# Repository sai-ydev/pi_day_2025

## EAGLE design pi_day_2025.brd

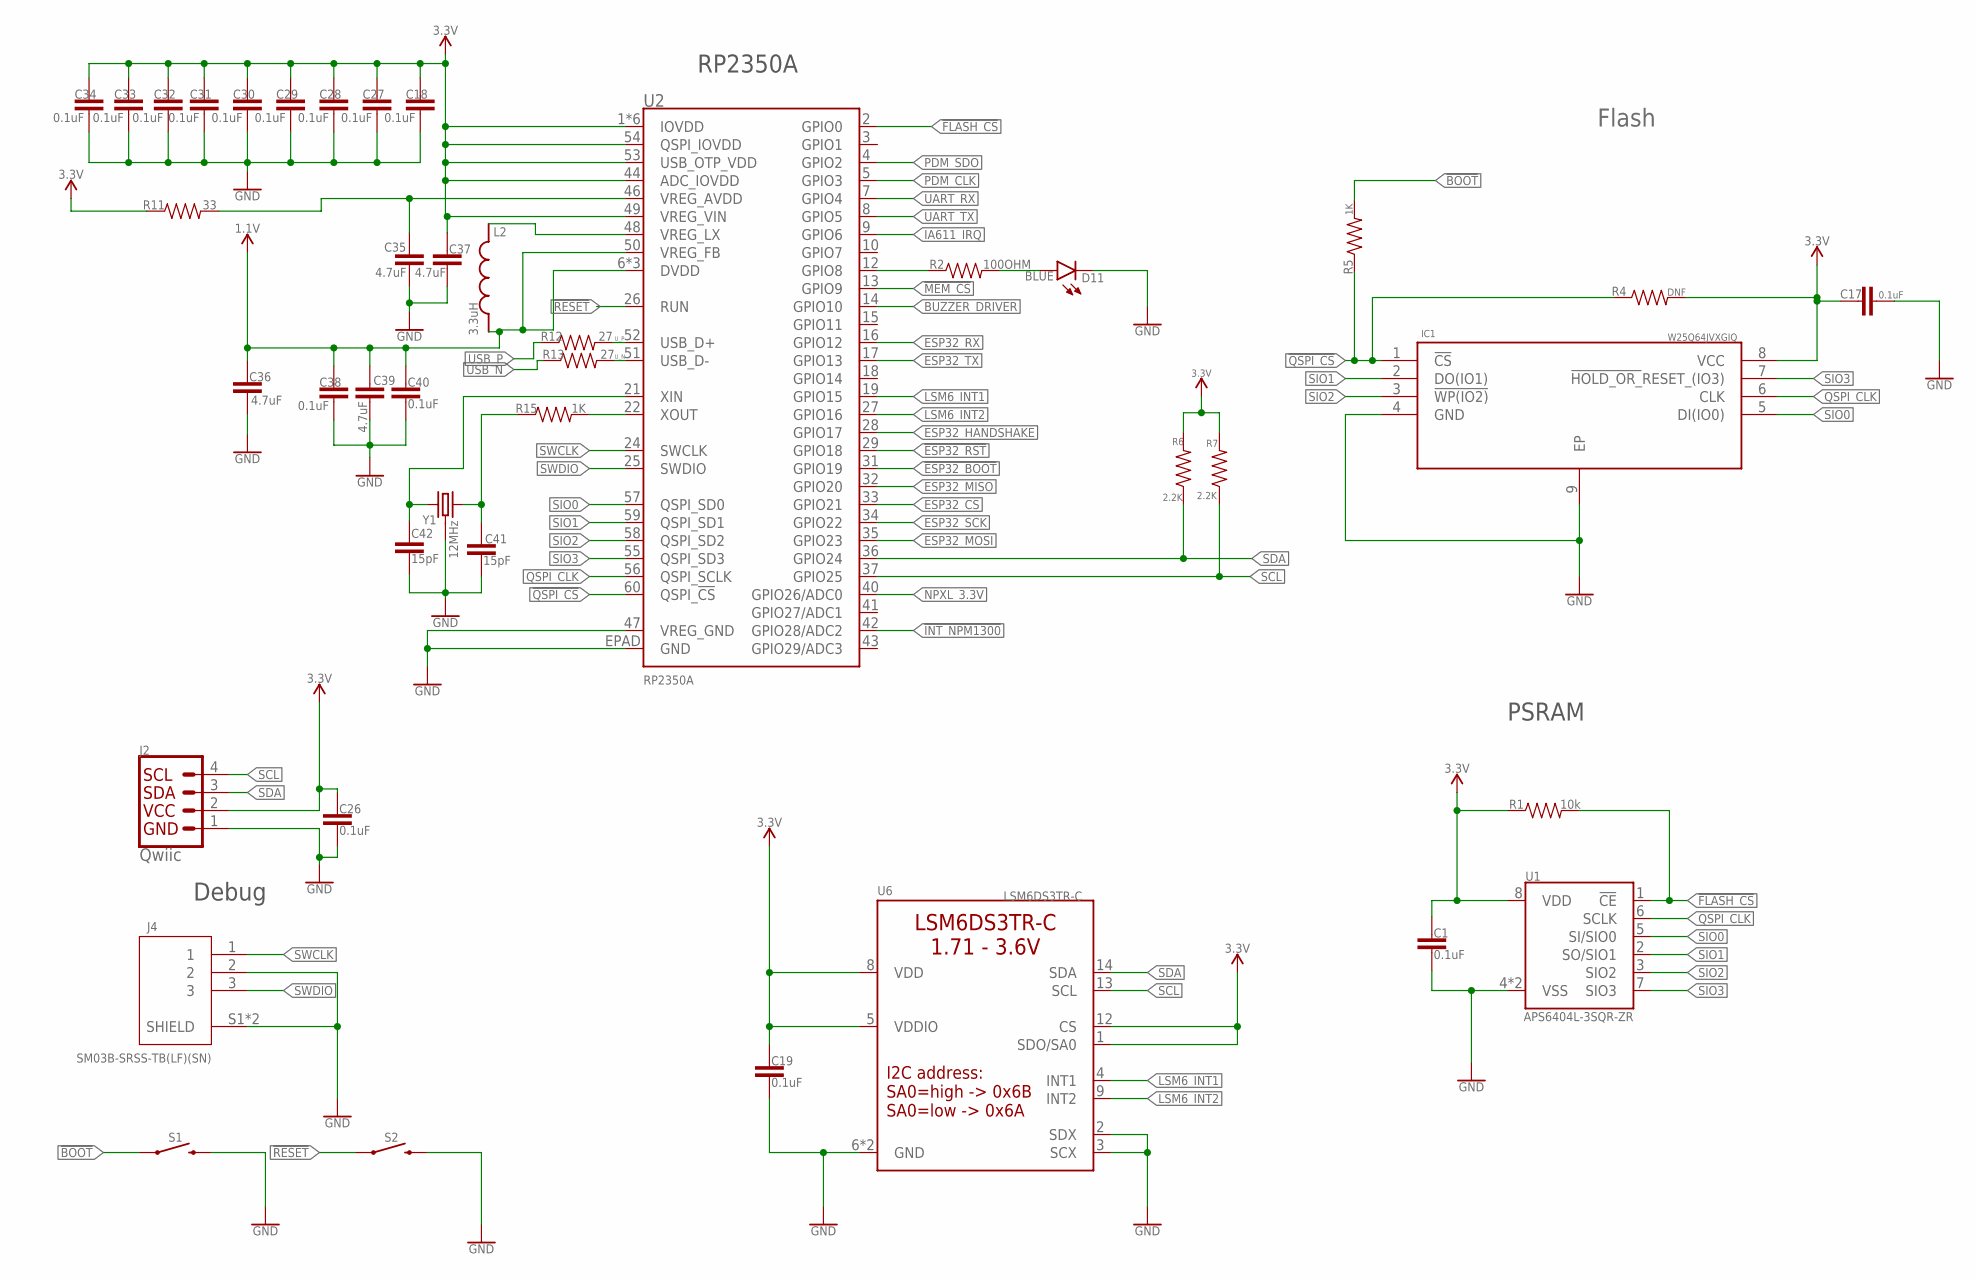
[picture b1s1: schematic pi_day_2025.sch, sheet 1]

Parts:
C1, C17, C18, C19, C26, C27, C28, C29, C30, C31, C32, C33, C34, C38, C40: 0.1uF; 0402
C35, C36, C37, C39: 4.7uF; 0402
C41, C42: 15pF; 0402
D11: BLUE; LED-0603
IC1: W25Q64JVXGIQ; SON80P400X400X50-9N
J2: Qwiic; 1X04_1MM_RA
J4: SM03B-SRSS-TB(LF)(SN); JST_SM03B-SRSS-TB(LF)(SN)
L2: 3.3uH; IND_LQH2MCN120K02L
R1: 10k; 0402
R2: 100OHM; 0402
R4: DNF; 0402
R5, R15: 1K; 0402
R6, R7: 2.2K; 0402
R11: 33; 0402
R12, R13: 27; 0402
S1, S2: MOMENTARY-SWITCH-SPST-SMD-4.6X2.8MM; TACTILE_SWITCH_SMD_4.6X2.8MM
U1: APS6404L-3SQR-ZR
U2: RP2350A
U6: LSM6DS3TR-C; LGA-14-2.5X3MM
Y1: 12MHz; CRYSTAL-SMD-3.2X2.5MM

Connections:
1.1V: C36.1, C38.1, C39.1, C40.1, L2.1, U2.6 (DVDD), U2.23 (DVDD), U2.39 (DVDD), U2.50 (VREG_FB)
3.3V: C1.1, C17.1, C18.1, C19.1, C26.1, C27.1, C28.1, C29.1, C30.1, C31.1, C32.1, C33.1, C34.1, C37.1, IC1.8 (VCC), J2.2, R1.1, R4.2, R6.2, R7.2, R11.1, U1.8 (VDD), U2.1 (IOVDD), U2.11 (IOVDD), U2.20 (IOVDD), U2.30 (IOVDD), U2.38 (IOVDD), U2.44 (ADC_IOVDD), U2.45 (IOVDD), U2.49 (VREG_VIN), U2.53 (USB_OTP_VDD), U2.54 (QSPI_IOVDD), U6.1 (SDO/SA0), U6.5 (VDDIO), U6.8 (VDD), U6.12 (CS); also elsewhere on the board
!BOOT: R5.2, S1.1, S1.2 (1)
!ESP32_BOOT: U2.31 (GPIO19); also elsewhere on the board
!ESP32_RST: U2.29 (GPIO18); also elsewhere on the board
!FLASH_CS: R1.2, U1.1 (!CE!), U2.2 (GPIO0)
!INT_NPM1300: U2.42 (GPIO28/ADC2); also elsewhere on the board
!MEM_CS: U2.13 (GPIO9); also elsewhere on the board
!QSPI_CS: IC1.1 (!CS), R4.1, R5.1, U2.60 (QSPI_!CS!)
!RESET: S2.1, S2.2 (1), U2.26 (RUN)
BUZZER_DRIVER: U2.14 (GPIO10); also elsewhere on the board
ESP32_CS: U2.33 (GPIO21); also elsewhere on the board
ESP32_HANDSHAKE: U2.28 (GPIO17); also elsewhere on the board
ESP32_MISO: U2.32 (GPIO20); also elsewhere on the board
ESP32_MOSI: U2.35 (GPIO23); also elsewhere on the board
ESP32_RX: U2.16 (GPIO12); also elsewhere on the board
ESP32_SCK: U2.34 (GPIO22); also elsewhere on the board
ESP32_TX: U2.17 (GPIO13); also elsewhere on the board
GND: C1.2, C17.2, C18.2, C19.2, C26.2, C27.2, C28.2, C29.2, C30.2, C31.2, C32.2, C33.2, C34.2, C35.2, C36.2, C37.2, C38.2, C39.2, C40.2, C41.2, C42.2, D11.C, IC1.4 (GND), IC1.9 (EP), J2.1, J4.2, J4.S1 (SHIELD), J4.S2 (SHIELD), S1.3 (2), S1.4 (2), S2.3 (2), S2.4 (2), U1.4 (VSS), U1.9 (VSS), U2.47 (VREG_GND), U2.EPAD (GND), U6.2 (SDX), U6.3 (SCX), U6.6 (GND), U6.7 (GND), Y1.2 (GND), Y1.4 (GND); also elsewhere on the board
IA611_IRQ: U2.9 (GPIO6); also elsewhere on the board
LSM6_INT1: U2.19 (GPIO15), U6.4 (INT1)
LSM6_INT2: U2.27 (GPIO16), U6.9 (INT2)
unnamed: R2.1, U2.12 (GPIO8)
unnamed: C35.1, R11.2, U2.46 (VREG_AVDD)
unnamed: D11.A, R2.2
unnamed: L2.2, U2.48 (VREG_LX)
unnamed: C41.1, R15.1, Y1.3 (2)
unnamed: C42.1, U2.21 (XIN), Y1.1
unnamed: R15.2, U2.22 (XOUT)
NPXL_3.3V: U2.40 (GPIO26/ADC0); also elsewhere on the board
PDM_CLK: U2.5 (GPIO3); also elsewhere on the board
PDM_SDO: U2.4 (GPIO2); also elsewhere on the board
QSPI_CLK: IC1.6 (CLK), U1.6 (SCLK), U2.56 (QSPI_SCLK)
SCL: J2.4, R7.1, U2.37 (GPIO25), U6.13 (SCL); also elsewhere on the board
SDA: J2.3, R6.1, U2.36 (GPIO24), U6.14 (SDA); also elsewhere on the board
SIO0: IC1.5 (DI(IO0)), U1.5 (SI/SIO0), U2.57 (QSPI_SD0)
SIO1: IC1.2 (DO(IO1)), U1.2 (SO/SIO1), U2.59 (QSPI_SD1)
SIO2: IC1.3 (!WP(IO2)), U1.3 (SIO2), U2.58 (QSPI_SD2)
SIO3: IC1.7 (!HOLD_OR_!RESET_(IO3)), U1.7 (SIO3), U2.55 (QSPI_SD3)
SWCLK: J4.1, U2.24 (SWCLK)
SWDIO: J4.3, U2.25 (SWDIO)
UART_RX: U2.7 (GPIO4); also elsewhere on the board
UART_TX: U2.8 (GPIO5); also elsewhere on the board
USB_N: R13.1; also elsewhere on the board
USB_P: R12.1; also elsewhere on the board
U_N: R13.2, U2.51 (USB_D-)
U_P: R12.2, U2.52 (USB_D+)

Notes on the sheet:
RP2350A
PSRAM
Flash
Debug

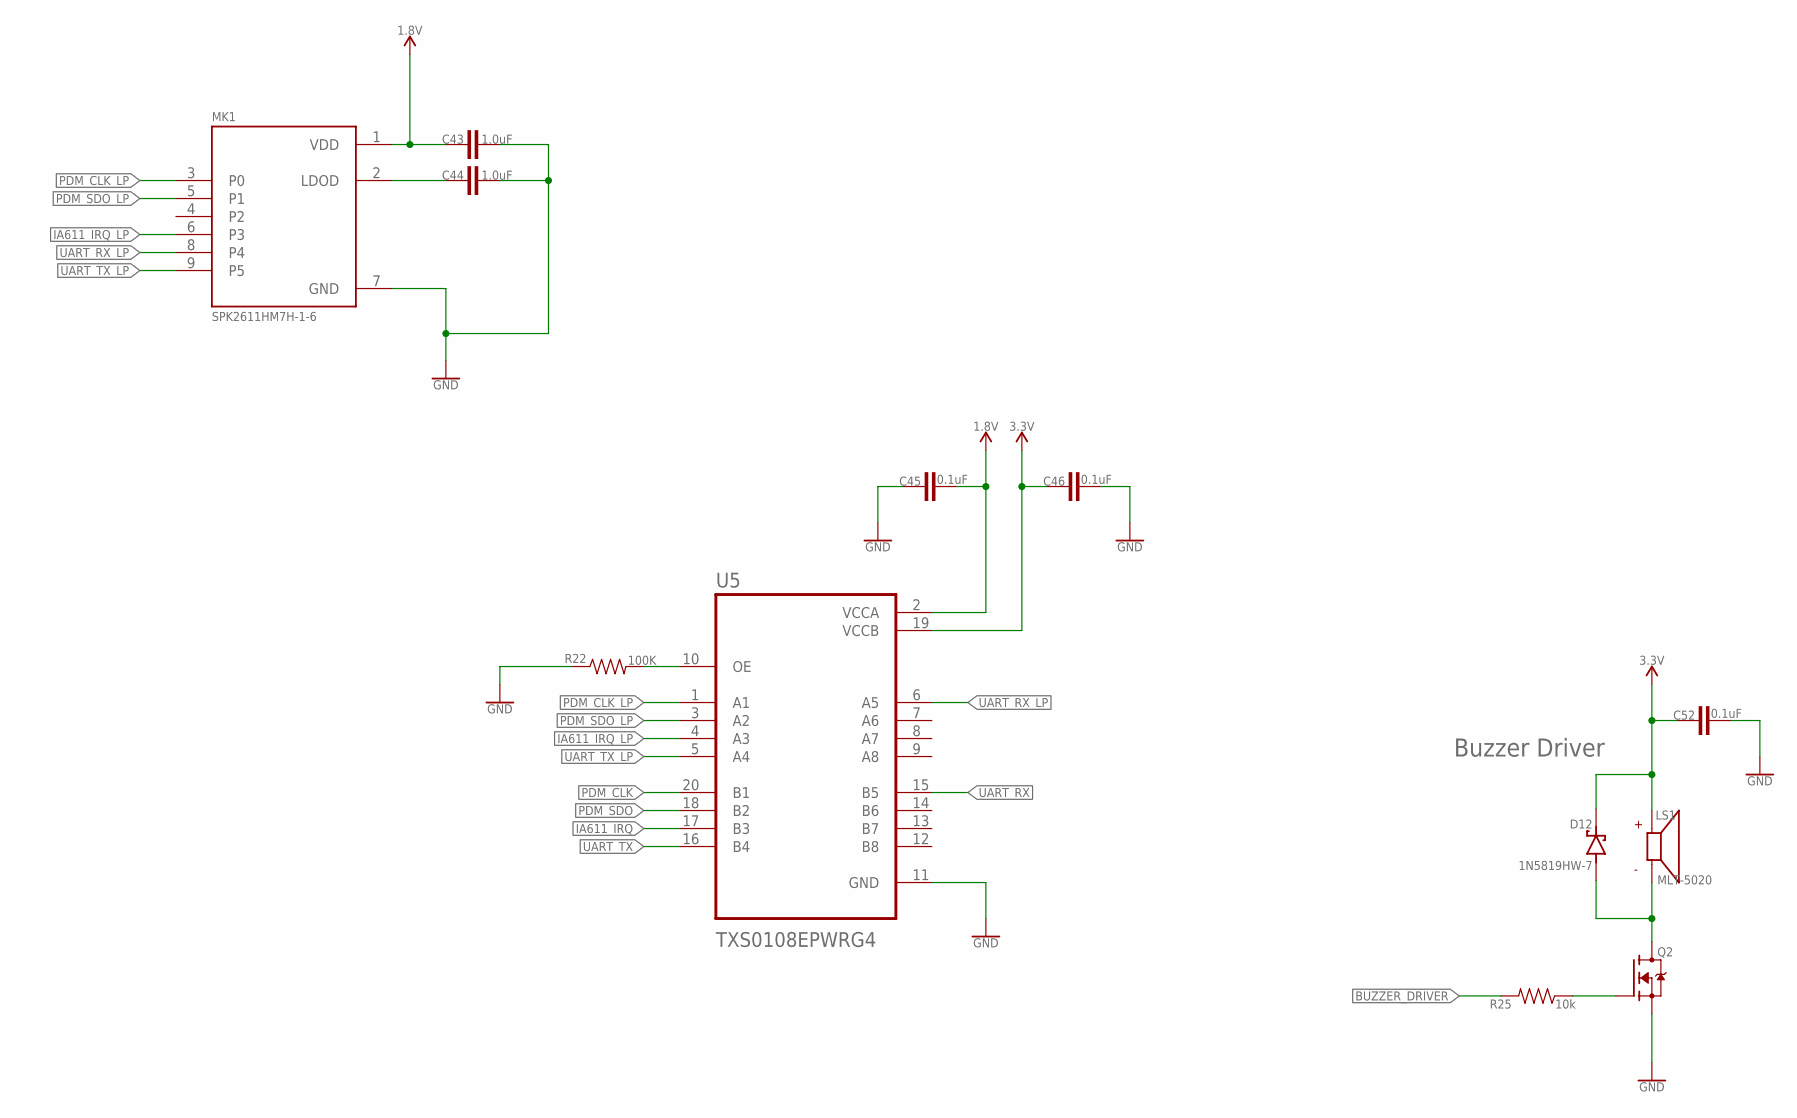
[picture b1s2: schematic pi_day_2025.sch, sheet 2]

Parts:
C43, C44: 1.0uF; 0402
C45, C46, C52: 0.1uF; 0402
D12: 1N5819HW-7; SOD3715X145N
LS1: MLT-5020; XDCR_CMT-8504-100-SMT-TR
MK1: SPK2611HM7H-1-6; MIC_SPK2611HM7H-1-6
Q2: BSS138; SOT95P240X111-3N
R22: 100K; 0402
R25: 10k; 0402
U5: TXS0108EPWRG4; SOP65P640X120-20N

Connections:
1.8V: C43.1, C45.2, MK1.1 (VDD), U5.2 (VCCA); also elsewhere on the board
3.3V: C46.1, C52.1, D12.C (K), LS1.P, U5.19 (VCCB); also elsewhere on the board
BUZZER_DRIVER: R25.2; also elsewhere on the board
GND: C43.2, C44.2, C45.1, C46.2, C52.2, MK1.7 (GND), Q2.2 (S), R22.1, U5.11 (GND); also elsewhere on the board
IA611_IRQ: U5.17 (B3); also elsewhere on the board
IA611_IRQ_LP: MK1.6 (P3), U5.4 (A3)
unnamed: C44.1, MK1.2 (LDOD)
unnamed: R22.2, U5.10 (OE)
unnamed: D12.A, LS1.N, Q2.3 (D)
unnamed: Q2.1 (G), R25.1
PDM_CLK: U5.20 (B1); also elsewhere on the board
PDM_CLK_LP: MK1.3 (P0), U5.1 (A1)
PDM_SDO: U5.18 (B2); also elsewhere on the board
PDM_SDO_LP: MK1.5 (P1), U5.3 (A2)
UART_RX: U5.15 (B5); also elsewhere on the board
UART_RX_LP: MK1.8 (P4), U5.6 (A5)
UART_TX: U5.16 (B4); also elsewhere on the board
UART_TX_LP: MK1.9 (P5), U5.5 (A4)

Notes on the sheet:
Buzzer Driver

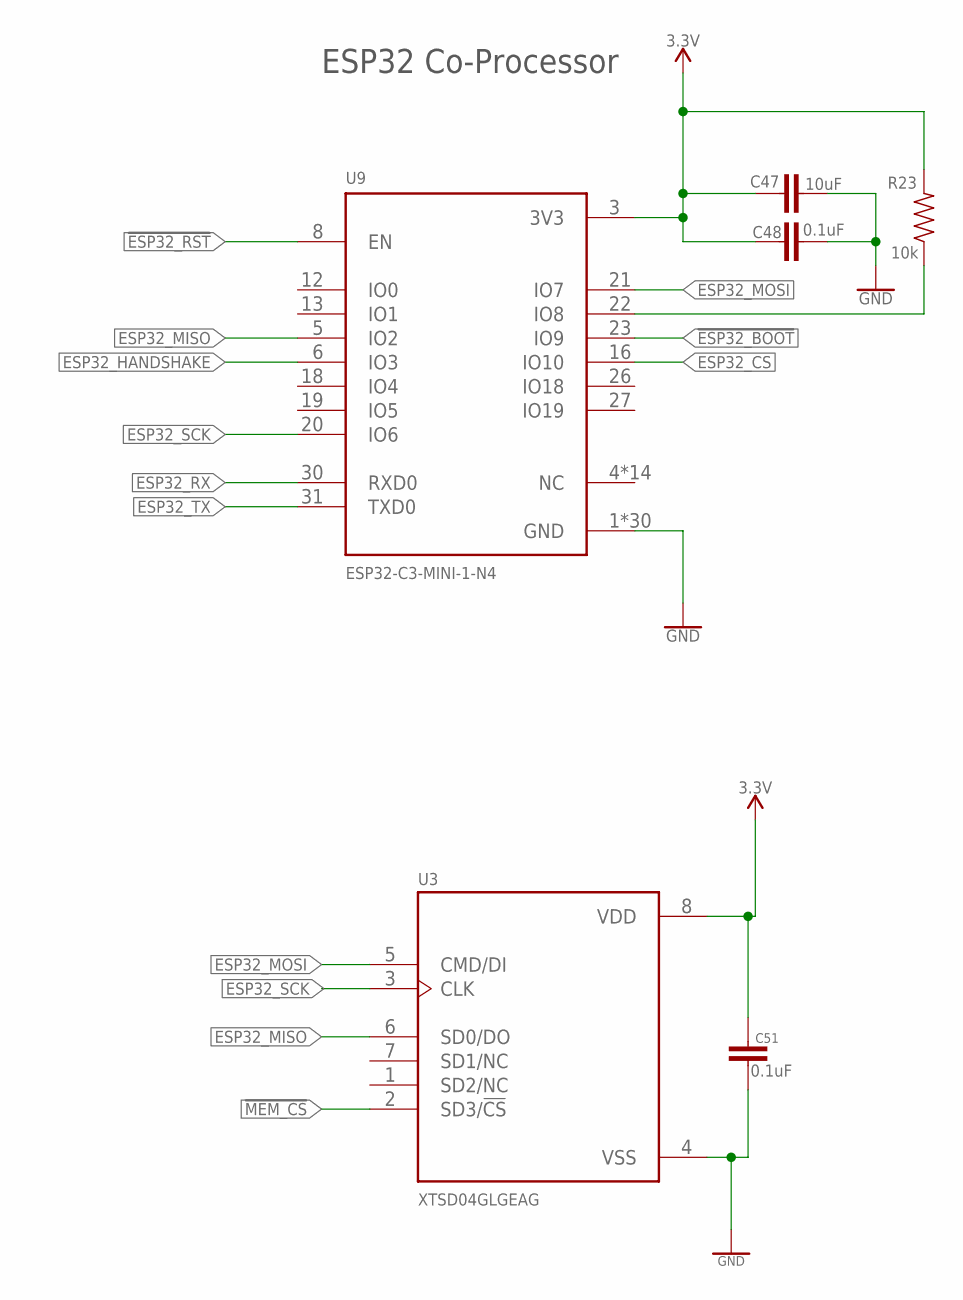
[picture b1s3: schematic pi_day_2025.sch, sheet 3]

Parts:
C47: 10uF; 0402-TIGHT
C48, C51: 0.1uF; 0402
R23: 10k; 0402
U3: XTSD04GLGEAG; SON127P600X800X95-8N
U9: ESP32-C3-MINI-1-N4; XCVR_ESP32-C3-MINI-1-N4

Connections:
3.3V: C47.1, C48.1, C51.2, R23.2, U3.8 (VDD), U9.3 (3V3); also elsewhere on the board
!ESP32_BOOT: U9.23 (IO9); also elsewhere on the board
!ESP32_RST: U9.8 (EN); also elsewhere on the board
!MEM_CS: U3.2 (SD3/!CS); also elsewhere on the board
ESP32_CS: U9.16 (IO10); also elsewhere on the board
ESP32_HANDSHAKE: U9.6 (IO3); also elsewhere on the board
ESP32_MISO: U3.6 (SD0/DO), U9.5 (IO2); also elsewhere on the board
ESP32_MOSI: U3.5 (CMD/DI), U9.21 (IO7); also elsewhere on the board
ESP32_RX: U9.30 (RXD0); also elsewhere on the board
ESP32_SCK: U3.3 (CLK), U9.20 (IO6); also elsewhere on the board
ESP32_TX: U9.31 (TXD0); also elsewhere on the board
GND: C47.2, C48.2, C51.1, U3.4 (VSS), U9.1 (GND), U9.2 (GND), U9.11 (GND), U9.14 (GND), U9.36 (GND), U9.37 (GND), U9.38 (GND), U9.39 (GND), U9.40 (GND), U9.41 (GND), U9.42 (GND), U9.43 (GND), U9.44 (GND), U9.45 (GND), U9.46 (GND), U9.47 (GND), U9.48 (GND), U9.49_1 (GND), U9.49_2 (GND), U9.49_3 (GND), U9.49_4 (GND), U9.49_5 (GND), U9.49_6 (GND), U9.49_7 (GND), U9.49_8 (GND), U9.49_9 (GND), U9.50 (GND), U9.51 (GND), U9.52 (GND), U9.53 (GND); also elsewhere on the board
unnamed: R23.1, U9.22 (IO8)

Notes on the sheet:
ESP32 Co-Processor

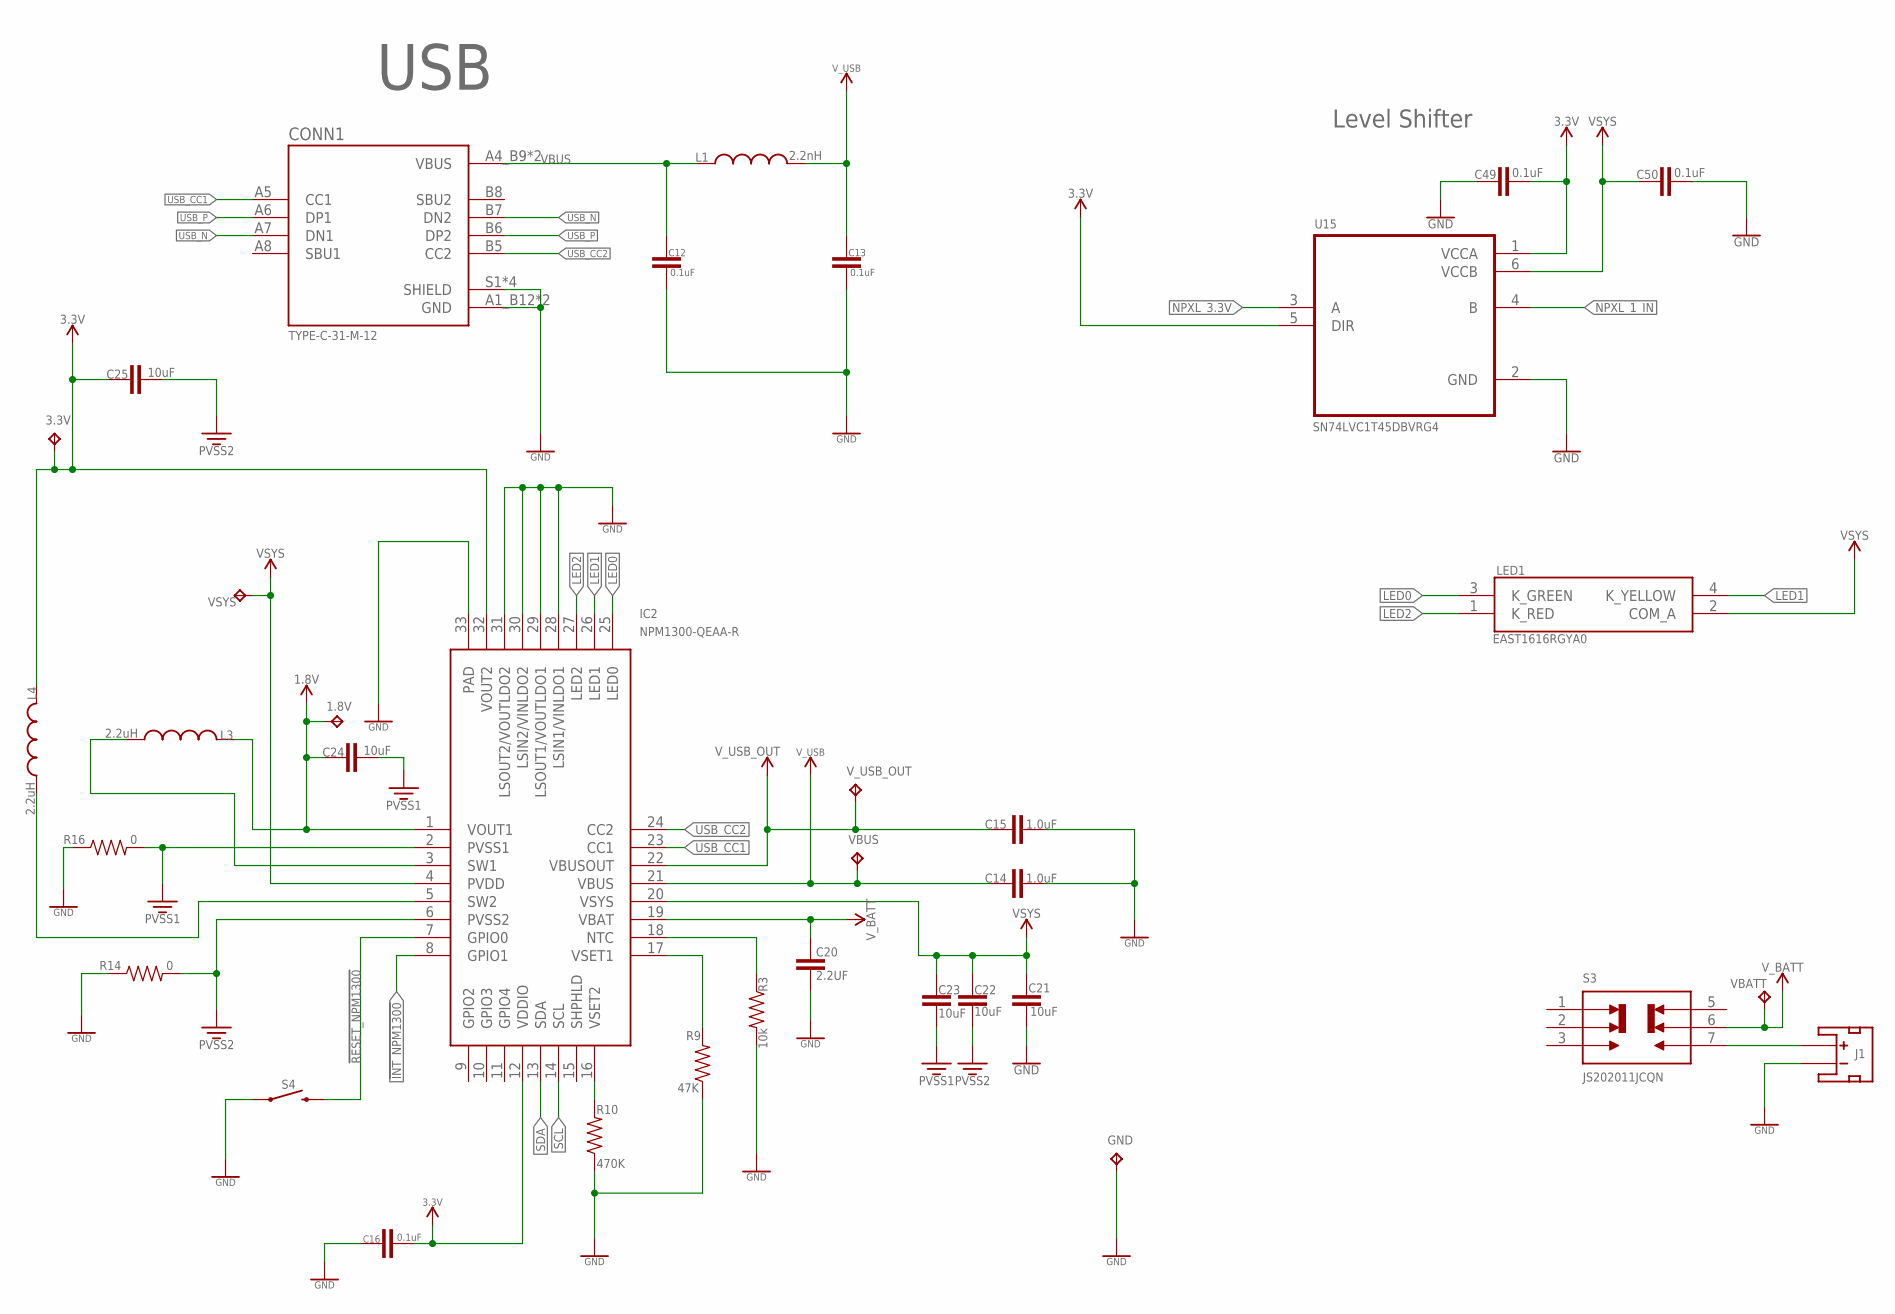
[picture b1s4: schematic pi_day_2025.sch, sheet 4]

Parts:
1.8V, 3.3V: TPB1,27; B1,27
C12, C13, C16, C49, C50: 0.1uF; 0402
C14, C15: 1.0uF; 0402
C20: 2.2UF; 0402
C21, C22, C23, C24, C25: 10uF; 0402
CONN1: TYPE-C-31-M-12; HRO_TYPE-C-31-M-12
GND: TPB1,27; B1,27
IC2: NPM1300-QEAA-R; QFN50P500X500X90-33N
J1: JST-PH=2; JST-2-SMD
L1: 2.2nH; INDC1608X100N
L3, L4: 2.2uH; INDC2016X100N
LED1: EAST1616RGYA0
R3: 10k; 0402
R9: 47K; 0402
R10: 470K; 0402
R14, R16: 0; 0402
S3: JS202011JCQN; SW_JS202011JCQN
S4: MOMENTARY-SWITCH-SPST-SMD-4.6X2.8MM; TACTILE_SWITCH_SMD_4.6X2.8MM
U15: SN74LVC1T45DBVRG4; SOT95P280X145-6N
VBATT: TPB1,27; B1,27
VBUS: TPB1,27; B1,27
VSYS: TPB1,27; B1,27
V_USB_OUT: TPB1,27; B1,27

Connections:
1.8V: 1.8V.TP, C24.1, IC2.1 (VOUT1), L3.2; also elsewhere on the board
3.3V: 3.3V.TP, C16.2, C25.1, C49.2, IC2.12 (VDDIO), IC2.32 (VOUT2), L4.2, U15.1 (VCCA), U15.5 (DIR); also elsewhere on the board
!INT_NPM1300: IC2.8 (GPIO1); also elsewhere on the board
!RESET_NPM1300: IC2.7 (GPIO0), S4.3 (2), S4.4 (2)
GND: C12.2, C13.2, C14.2, C15.2, C16.1, C20.2, C21.2, C49.1, C50.2, CONN1.A1_B12 (GND), CONN1.B1_A12 (GND), CONN1.S1 (SHIELD), CONN1.S2 (SHIELD), CONN1.S3 (SHIELD), CONN1.S4 (SHIELD), GND.TP, IC2.28 (LSIN1/VINLDO1), IC2.29 (LSOUT1/VOUTLDO1), IC2.30 (LSIN2/VINLDO2), IC2.31 (LSOUT2/VOUTLDO2), IC2.33 (PAD), J1.1 (-), R3.2, R9.1, R10.1, R14.1, R16.1, S4.1, S4.2 (1), U15.2 (GND); also elsewhere on the board
LED0: IC2.25 (LED0), LED1.3 (K_GREEN)
LED1: IC2.26 (LED1), LED1.4 (K_YELLOW)
LED2: IC2.27 (LED2), LED1.1 (K_RED)
unnamed: IC2.18 (NTC), R3.1
unnamed: IC2.16 (VSET2), R10.2
unnamed: IC2.17 (VSET1), R9.2
unnamed: J1.2 (+), S3.7
unnamed: IC2.3 (SW1), L3.1
unnamed: IC2.5 (SW2), L4.1
NPXL_1_IN: U15.4 (B); also elsewhere on the board
NPXL_3.3V: U15.3 (A); also elsewhere on the board
PVSS1: C23.2, C24.2, IC2.2 (PVSS1), R16.2
PVSS2: C22.2, C25.2, IC2.6 (PVSS2), R14.2
SCL: IC2.14 (SCL); also elsewhere on the board
SDA: IC2.13 (SDA); also elsewhere on the board
USB_CC1: CONN1.A5 (CC1), IC2.23 (CC1)
USB_CC2: CONN1.B5 (CC2), IC2.24 (CC2)
USB_N: CONN1.A7 (DN1), CONN1.B7 (DN2); also elsewhere on the board
USB_P: CONN1.A6 (DP1), CONN1.B6 (DP2); also elsewhere on the board
VBUS: C12.1, CONN1.A4_B9 (VBUS), CONN1.B4_A9 (VBUS), L1.1
VSYS: C21.1, C22.1, C23.1, C50.1, IC2.4 (PVDD), IC2.20 (VSYS), LED1.2 (COM_A), U15.6 (VCCB), VSYS.TP; also elsewhere on the board
V_BATT: C20.1, IC2.19 (VBAT), S3.6, VBATT.TP
V_USB: C13.1, C14.1, IC2.21 (VBUS), L1.2, VBUS.TP
V_USB_OUT: C15.1, IC2.22 (VBUSOUT), V_USB_OUT.TP

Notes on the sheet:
USB
Level Shifter

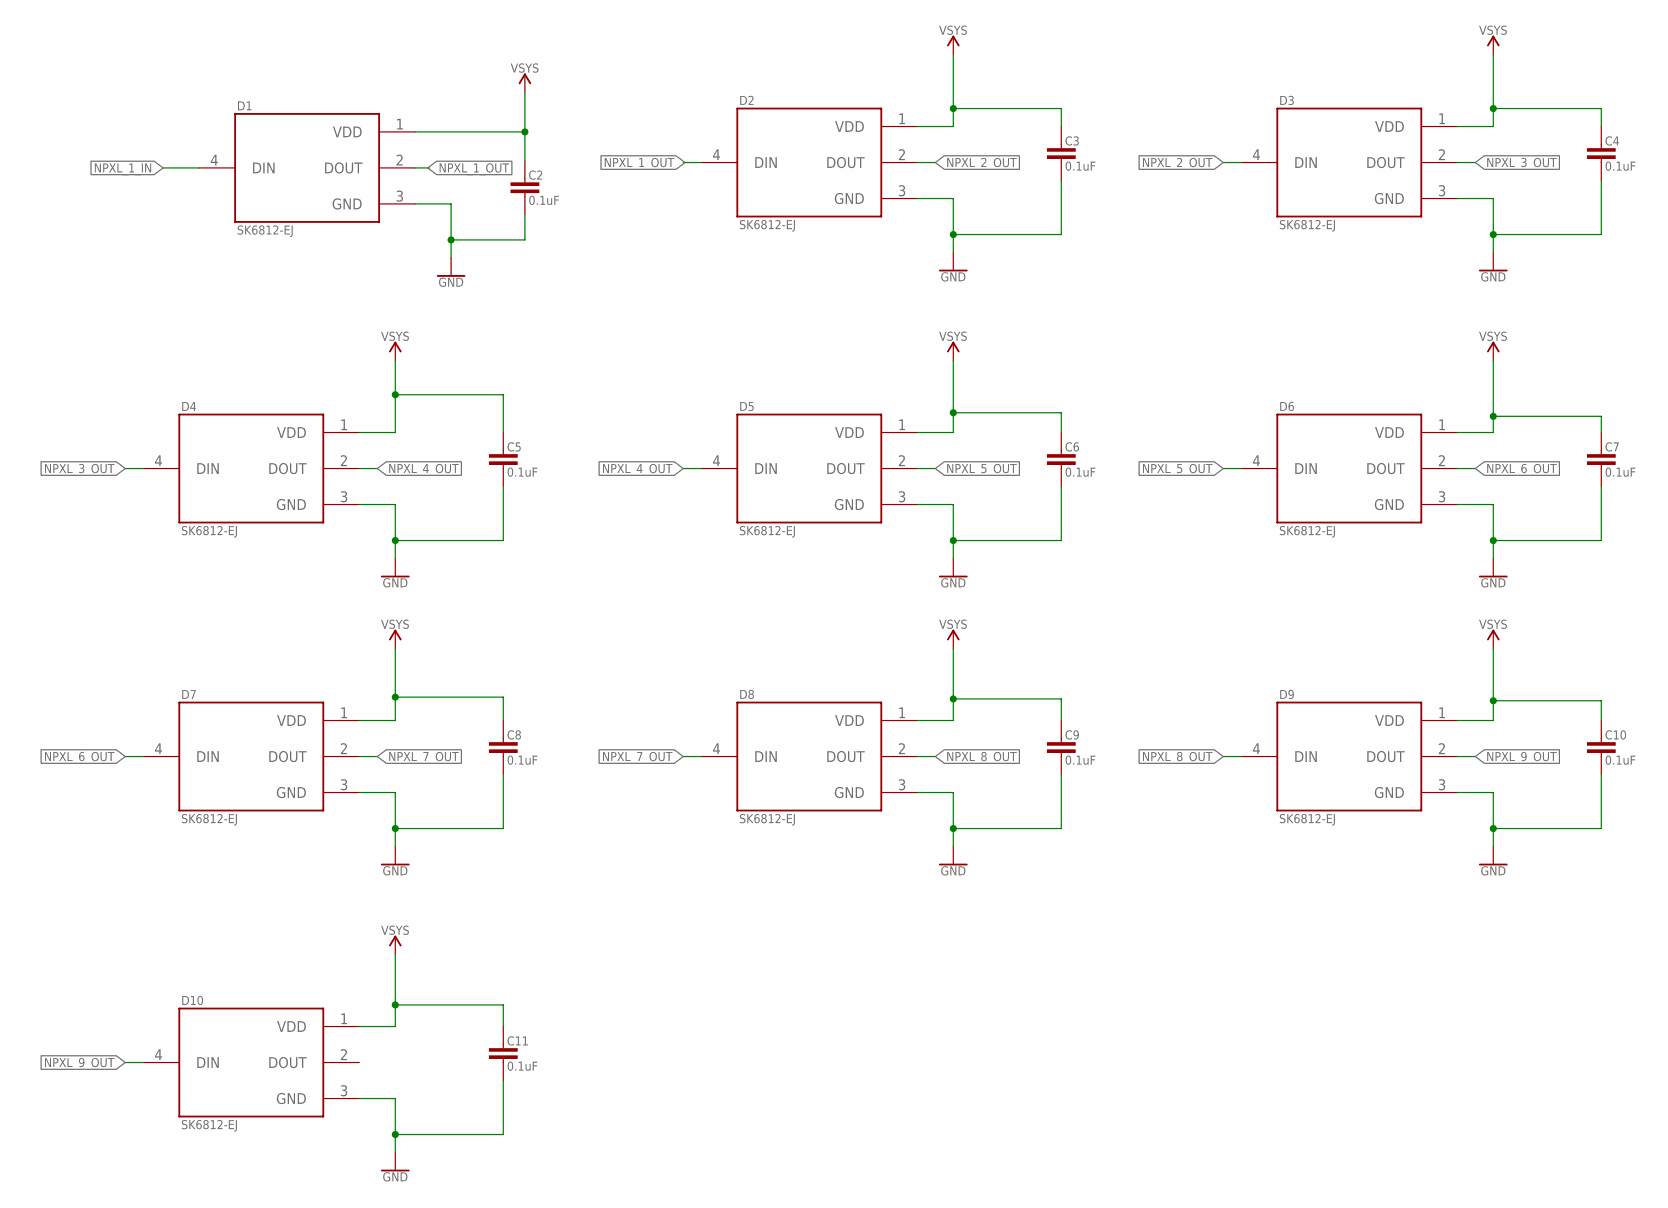
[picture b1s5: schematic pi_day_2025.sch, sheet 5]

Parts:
C2, C3, C4, C5, C6, C7, C8, C9, C10, C11: 0.1uF; 0402
D1, D2, D3, D4, D5, D6, D7, D8, D9, D10: SK6812-EJ; LED_SK6812-E

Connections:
GND: C2.2, C3.2, C4.2, C5.2, C6.2, C7.2, C8.2, C9.2, C10.2, C11.2, D1.3 (GND), D2.3 (GND), D3.3 (GND), D4.3 (GND), D5.3 (GND), D6.3 (GND), D7.3 (GND), D8.3 (GND), D9.3 (GND), D10.3 (GND); also elsewhere on the board
NPXL_1_IN: D1.4 (DIN); also elsewhere on the board
NPXL_1_OUT: D1.2 (DOUT), D2.4 (DIN)
NPXL_2_OUT: D2.2 (DOUT), D3.4 (DIN)
NPXL_3_OUT: D3.2 (DOUT), D4.4 (DIN)
NPXL_4_OUT: D4.2 (DOUT), D5.4 (DIN)
NPXL_5_OUT: D5.2 (DOUT), D6.4 (DIN)
NPXL_6_OUT: D6.2 (DOUT), D7.4 (DIN)
NPXL_7_OUT: D7.2 (DOUT), D8.4 (DIN)
NPXL_8_OUT: D8.2 (DOUT), D9.4 (DIN)
NPXL_9_OUT: D9.2 (DOUT), D10.4 (DIN)
VSYS: C2.1, C3.1, C4.1, C5.1, C6.1, C7.1, C8.1, C9.1, C10.1, C11.1, D1.1 (VDD), D2.1 (VDD), D3.1 (VDD), D4.1 (VDD), D5.1 (VDD), D6.1 (VDD), D7.1 (VDD), D8.1 (VDD), D9.1 (VDD), D10.1 (VDD); also elsewhere on the board

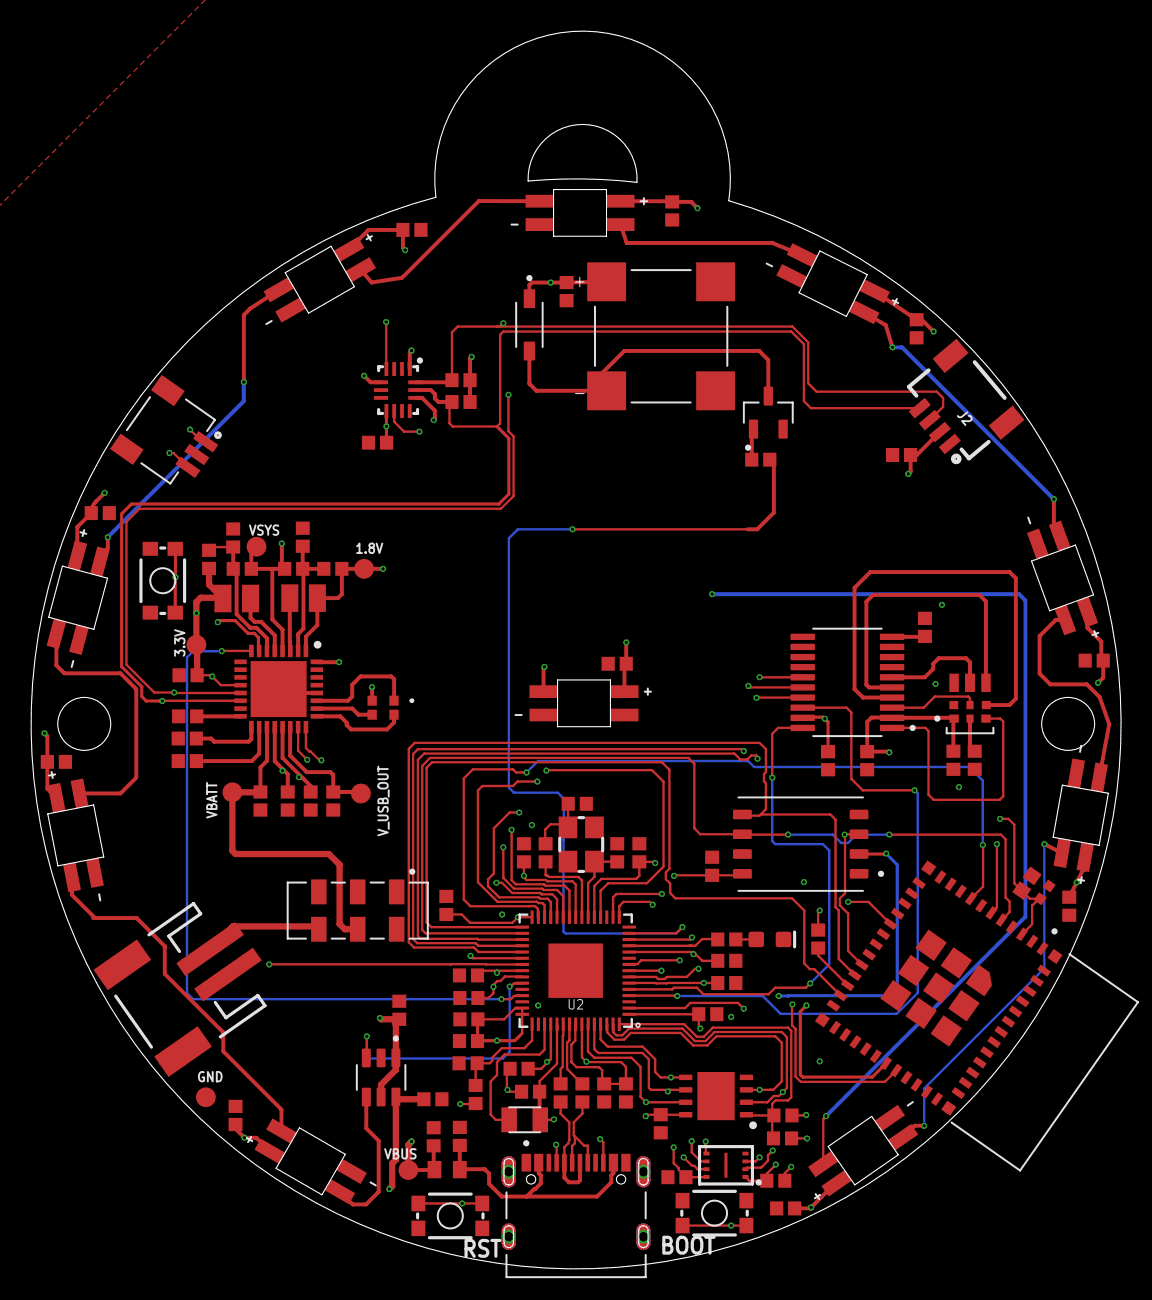
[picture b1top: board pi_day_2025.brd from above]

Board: 4 copper layers, 70.0 x 79.5 mm, 115 parts (0 on the bottom side), 87 nets.

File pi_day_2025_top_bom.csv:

Comment,Designator,Footprint,LCSC Part #
0,R14 R16,0402,
0.1uF,C1 C2 C3 C4 C5 C6 C7 C8 C9 C10 C11 C12 C13 C16 C17 C18 C19 C26 C27 C28 C29 C30 C31 C32 C33 C34 C38 C40 C45 C46 C48 C49 C50 C51 C52,0402,
1.0uF,C14 C15 C43 C44,0402,
1K,R5 R15,0402,
1N5819HW-7,D12,SOD3715X145N,
2.2K,R6 R7,0402,
2.2UF,C20,0402,
2.2nH,L1,INDC1608X100N,
2.2uH,L3 L4,INDC2016X100N,
3.3uH,L2,IND_LQH2MCN120K02L,
4.7uF,C35 C36 C37 C39,0402,
10k,R1 R3 R23 R25,0402,
10uF,C21 C22 C23 C24 C25,0402,
10uF,C47,0402-TIGHT,
12MHz,Y1,CRYSTAL-SMD-3.2X2.5MM,
15pF,C41 C42,0402,
27,R12 R13,0402,
33,R11,0402,
47K,R9,0402,
100K,R22,0402,
100OHM,R2,0402,
470K,R10,0402,
APS6404L-3SQR-ZR,U1,APS6404L-3SQR-ZR,
BLUE,D11,LED-0603,
BSS138,Q2,SOT95P240X111-3N,
DNF,R4,0402,
EAST1616RGYA0,LED1,EAST1616RGYA0,
ESP32-C3-MINI-1-N4,U9,XCVR_ESP32-C3-MINI-1-N4,
JS202011JCQN,S3,SW_JS202011JCQN,
JST-PH=2,J1,JST-2-SMD,
LSM6DS3TR-C,U6,LGA-14-2.5X3MM,
MLT-5020,LS1,XDCR_CMT-8504-100-SMT-TR,
MOMENTARY-SWITCH-SPST-SMD-4.6X2.8MM,S1 S2 S4,TACTILE_SWITCH_SMD_4.6X2.8MM,
NPM1300-QEAA-R,IC2,QFN50P500X500X90-33N,
Qwiic,J2,1X04_1MM_RA,
RP2350A,U2,RP2350A,
SK6812-EJ,D1 D2 D3 D4 D5 D6 D7 D8 D9 D10,LED_SK6812-E,
SM03B-SRSS-TB(LF)(SN),J4,JST_SM03B-SRSS-TB(LF)(SN),
SN74LVC1T45DBVRG4,U15,SOT95P280X145-6N,
SPK2611HM7H-1-6,MK1,MIC_SPK2611HM7H-1-6,
TPB1 27,1.8V,B1 27,
TPB1 27,3.3V,B1 27,
TPB1 27,GND,B1 27,
TPB1 27,VBATT,B1 27,
TPB1 27,VBUS,B1 27,
TPB1 27,VSYS,B1 27,
TPB1 27,V_USB_OUT,B1 27,
TXS0108EPWRG4,U5,SOP65P640X120-20N,
TYPE-C-31-M-12,CONN1,HRO_TYPE-C-31-M-12,
W25Q64JVXGIQ,IC1,SON80P400X400X50-9N,
XTSD04GLGEAG,U3,SON127P600X800X95-8N,

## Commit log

2025-01-16 design file check-in
2025-01-18 Updates to design
2025-01-19 File upload
2025-01-20 Check-in
2025-01-21 Finished power supply design
2025-01-21 Added 1.8V regulator
2025-01-21 Added bypass capacitor to IA611
2025-01-21 additions to txs0108
2025-01-22 Added pinouts for IA611 & voltage level converter
2025-01-22 Added PDM microphone
2025-01-22 Added ESP32 chipset.
2025-01-23 COmpleted schematic
2025-01-23 Finished schematic
2025-01-23 Replaced components
2025-01-24 Placed components
2025-02-02 Added voltage symbols
2025-02-02 more modification
2025-02-21 Checking in
2025-03-13 Checkin
2025-03-15 Firmware check-in
2025-03-15 Deleting files
2025-03-15 Completed Pendant

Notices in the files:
parts and their libraries:
SparkFun-Capacitors: Licensing: Creative Commons ShareAlike 4.0 International - https://creativecommons.org/licenses/by-sa/4.0
